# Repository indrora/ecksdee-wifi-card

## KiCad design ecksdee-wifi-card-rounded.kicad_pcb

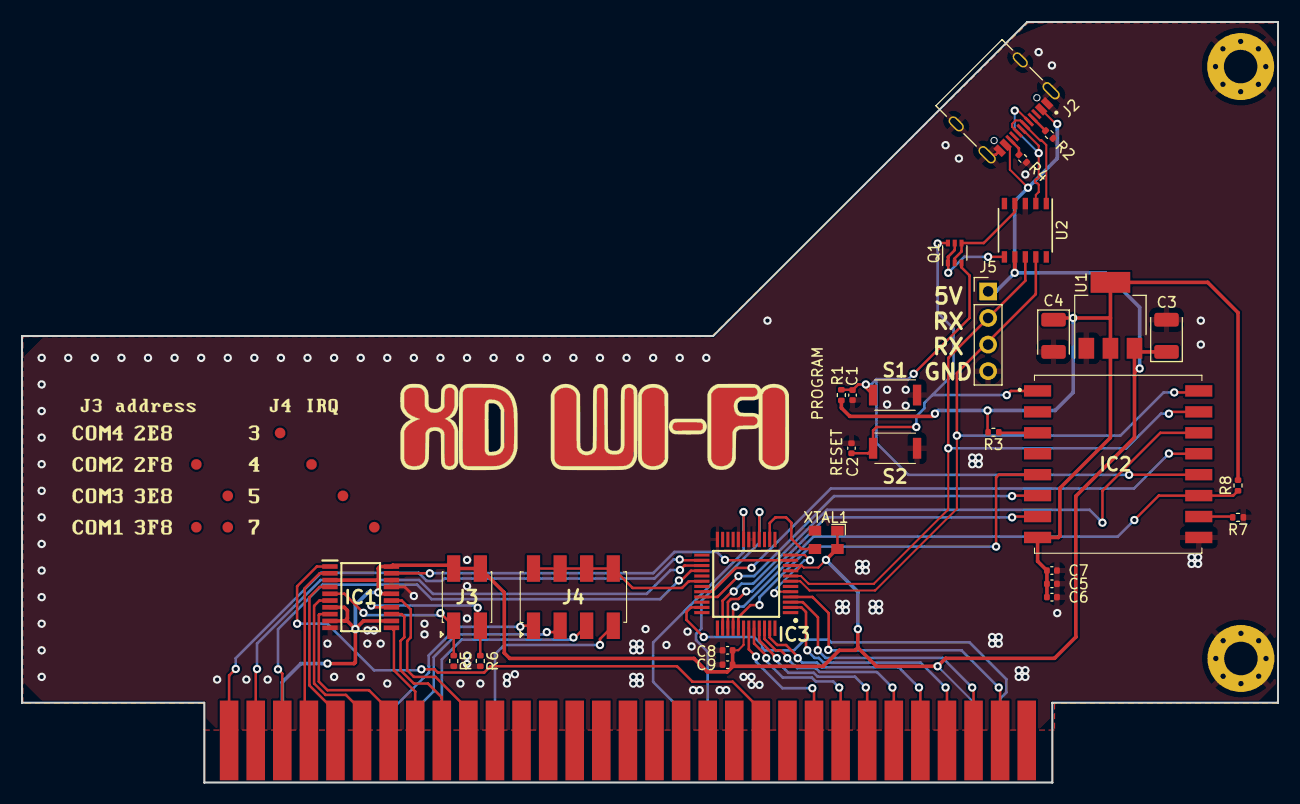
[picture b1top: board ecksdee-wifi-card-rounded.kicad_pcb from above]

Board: 2 copper layers, 120.0 x 72.7 mm, 36 parts (1 on the bottom side), 53 nets.

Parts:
C1, C2, C6, C7, C8: 0.1uF; C_0402_1005Metric
C3: 10uF; CP_EIA-3528-15_AVX-H
C4: 22uF; CP_EIA-3528-15_AVX-H
C5, C9: 1uF; C_0402_1005Metric
H1, H2: MountingHole_Pad; MountingHole_3.2mm_M3_Pad_Via
IC1: SN74HC688PWR; SOP65P640X120-20N
IC2: ESP-07S; ESP07S
IC3: TL16C550CPTR; QFP50P900X900X160-48N
J1: Bus_ISA_8bit; Conn_Edge_PCB_ISA8
J2: TYPE-C-31-M-12; HRO_TYPE-C-31-M-12
J3: 95278-101A04LF; 95278101A04LF
J4: 95278-801A08LF; 95278801A08LF
J5: Conn_01x04; PinHeader_1x04_P2.54mm_Vertical
Q1: UMH3N; SOT-363_SC-70-6
R1, R2, R3, R4, R5, R6, R7, R8: 5.1K; R_0402_1005Metric
Ref**: Val**; logo
Ref**#2: Val**; addr-irq
Ref**#3: Val**; back
S1, S2: SKRKAEE020
U1: AMS1117-3.3; SOT-223-3_TabPin2
U2: CH340K; SSOP-10_3.9x4.9mm_P1.00mm
XTAL1: S3D1.843200B20F30T; SMD3225-4P

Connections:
+3V3: C4.1, C5.1, C6.1, C7.1, IC2.8 (VCC), R1.2, R3.2, R8.2, U1.2 (VO)
/ESP_GPIO0: C1.1, IC2.12 (GPIO0), Q1.3 (C2), R1.1, S1.2
/ESP_GPIO2: IC2.11 (GPIO2), IC3.40 (~DCD), R8.1
/ESP_GPIO4: IC2.13 (GPIO4), IC3.32 (~RTS)
/ESP_GPIO5: IC2.14 (GPIO5), IC3.38 (~CTS)
/ESP_GPIO12: IC2.6 (GPIO12), IC3.33 (~DTR)
/ESP_GPIO13: IC2.7 (GPIO13), IC3.39 (~DSR)
/ESP_GPIO14: IC2.5 (GPIO14), IC3.41 (~RI)
/ESP_GPIO15: IC2.10 (GPIO15), R7.2
/ESP_RST: C2.1, IC2.1 (RST), Q1.6 (C1), S2.2
/ISA_ADDR0: IC3.28 (A0), J1.60 (BA02)
/ISA_ADDR1: IC3.27 (A1), J1.61 (BA01)
/ISA_ADDR2: IC3.26 (A2), J1.62 (BA00)
/ISA_ADDR3: IC1.2 (P0), J1.59 (BA03)
/ISA_ADDR4: IC1.4 (P1), J1.58 (BA04)
/ISA_ADDR5: IC1.6 (P2), J1.57 (BA05)
/ISA_ADDR6: IC1.8 (P3), J1.56 (BA06)
/ISA_ADDR7: IC1.11 (P4), J1.55 (BA07)
/ISA_ADDR8: IC1.13 (P5), J1.54 (BA08)
/ISA_ADDR9: IC1.15 (P6), J1.53 (BA09)
/ISA_D0: IC3.43 (D0), J1.40 (DB0)
/ISA_D1: IC3.44 (D1), J1.39 (DB1)
/ISA_D2: IC3.45 (D2), J1.38 (DB2)
/ISA_D3: IC3.46 (D3), J1.37 (DB3)
/ISA_D4: IC3.47 (D4), J1.36 (DB4)
/ISA_D5: IC3.2 (D5), J1.35 (DB5)
/ISA_D6: IC3.3 (D6), J1.34 (DB6)
/ISA_D7: IC3.4 (D7), J1.33 (DB7)
/ISA_ENABLE: IC1.1 (~OE), J1.42 (AEN)
/ISA_IOR: IC3.19 (~RD1), J1.14 (~IOR)
/ISA_IOW: IC3.16 (~WR1), J1.13 (~IOW)
/ISA_IRQ3: J1.25 (IRQ3), J4.1
/ISA_IRQ4: J1.24 (IRQ4), J4.3
/ISA_IRQ5: J1.23 (IRQ5), J4.5
/ISA_IRQ7: J1.21 (IRQ7), J4.7
/ISA_RESET: IC3.35 (MR), J1.2 (RESET)
/UART_CLOCK: IC3.14 (XIN), XTAL1.3 (OUT)
/UART_IRQ: IC3.30 (INTRPT), J4.2, J4.4, J4.6, J4.8
/UART_RX: IC2.16 (TXD0), IC3.7 (SIN), J5.3, U2.9 (RXD)
/UART_SEL4: IC1.5 (Q1), J3.1, R5.1
/UART_SEL8: IC1.14 (Q5), J3.3, R6.1
/UART_TX: IC2.15 (RXD0), IC3.8 (SOUT), J5.2, U2.8 (TXD)
/USB_D+: J2.A6 (DP1), J2.B6 (DP2), U2.1 (UD+)
/USB_D-: J2.A7 (DN1), J2.B7 (DN2), U2.2 (UD-)
/USB_DTR: Q1.2 (B1), Q1.4 (E2), U2.4 (~DTR)
/USB_RTS: Q1.1 (E1), Q1.5 (B2), U2.6 (~RTS)
/~UART_SEL: IC1.19 (~P=Q), IC3.11 (~CS2)
GND: C1.2, C2.2, C3.2, C4.2, C5.2, C6.2, C7.2, C8.2, C9.2, H1.1, H2.1, IC1.10 (GND), IC1.17 (P7), IC1.18 (Q7), IC2.9 (GND), IC3.17 (WR2), IC3.18 (VSS), IC3.20 (RD2), IC3.24 (~ADS), J1.1 (GND), J1.10 (GND), J1.31 (GND), J2.A1/B12 (GND), J2.B1/A12 (GND), J2.S1 (SHIELD), J2.S2 (SHIELD), J2.S3 (SHIELD), J2.S4 (SHIELD), J5.4, R2.1, R4.1, R5.2, R6.2, R7.1, S1.1, S2.1, U1.1 (GND), U2.3 (GND), XTAL1.2 (GND)
unnamed: IC2.3 (EN), R3.1
unnamed: IC3.5 (RCLK), IC3.12 (~BAUDOUT)
unnamed: J2.A5 (CC1), R2.2
unnamed: J2.B5 (CC2), R4.2
VCC: C3.1, C8.1, C9.1, IC1.3 (Q0), IC1.7 (Q2), IC1.9 (Q3), IC1.12 (Q4), IC1.16 (Q6), IC1.20 (VCC), IC3.9 (CS0), IC3.10 (CS1), IC3.42 (VCC), J1.3 (VCC), J1.29 (VCC), J2.A4/B9 (VBUS), J2.B4/A9 (VBUS), J3.2, J3.4, J5.1, U1.3 (VI), U2.7 (VCC), XTAL1.1 (EN), XTAL1.4 (VIN)
